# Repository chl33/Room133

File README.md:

# Room133 (v1.0.0)

Room133 is an ESP32-based family of devices which helps with various room-monitoring tasks, particulary for use with [Home Assistant](https://www.home-assistant.io/).

## Features
- **Adaptive Web Interface:** A modern, responsive Svelte UI that automatically detects and displays only the hardware capabilities active on your specific board (Motion, Light, Leak, OLED).
- **Climate Monitoring:** SHTC3-based temperature and humidity tracking.
- **Motion & Presence:** Support for one or more PIR sensors.
- **Environmental Sensing:** Light level measurement and standing water (leak) detection.
- **Unified Configuration:** Standardized JSON API and a clean settings interface for tuning filters and thresholds.
- **Robust Networking:** Automatic captive portal for WiFi setup and auto-reboot on configuration changes.
- **OTA Updates:** Reliable wireless firmware updates (requires `min_spiffs.csv` partition layout).

It is based on the [og3](https://github.com/chl33/og3) C++ software framework.

This repository includes software for the device, KiCAD files for the circuit board, and OpenSCAD files for creating the project boxes for the different devices.

Please see the [write-up](https://selectiveappeal.org/posts/room133/) on the project in my blog.  I also [wrote about](https://selectiveappeal.org/posts/room133-box/) the EBox design included in this repository.

## PCBA design: KiCAD

This project contains KiCAD sources for the Room133 circuit board.  It requires the [chl33_kicad_sym](https://github.com/chl33/chl33_kicad_sym) library.  I'm not experienced with sharing KiCAD projects in github.  I expect you will need to fix some path names if you try to open this project in KiCAD.

## EBox design: OpenSCAD

This project contains OpenSCAD sources for 3D-printing EBoxes for Room133 devices.  They use the library in [ProjectBox](https://github.com/chl33/ProjectBox).

You can open [`Ebox/Room133_test.scad`](Ebox/Room133_test.scad) with OpenSCAD and run [`Ebox/gui.sh`](Ebox/gui.sh), and use the user interface to customize the box depending on the application

.

I slice my EBox models with PrusaSlicer and print them in PETG.

## Wires

### PIR wire

JST socket 3x1

| Pin 1 | Pin2 | Pin 3  |
|:------|:-----|:-------|
| +5V   | GND  | Motion |

to

Dupont socket 3x1

| Pin 1 | Pin2 |  Pin 3  |
|:------|:------|:-------|
| +5V   | Motion| GND    |

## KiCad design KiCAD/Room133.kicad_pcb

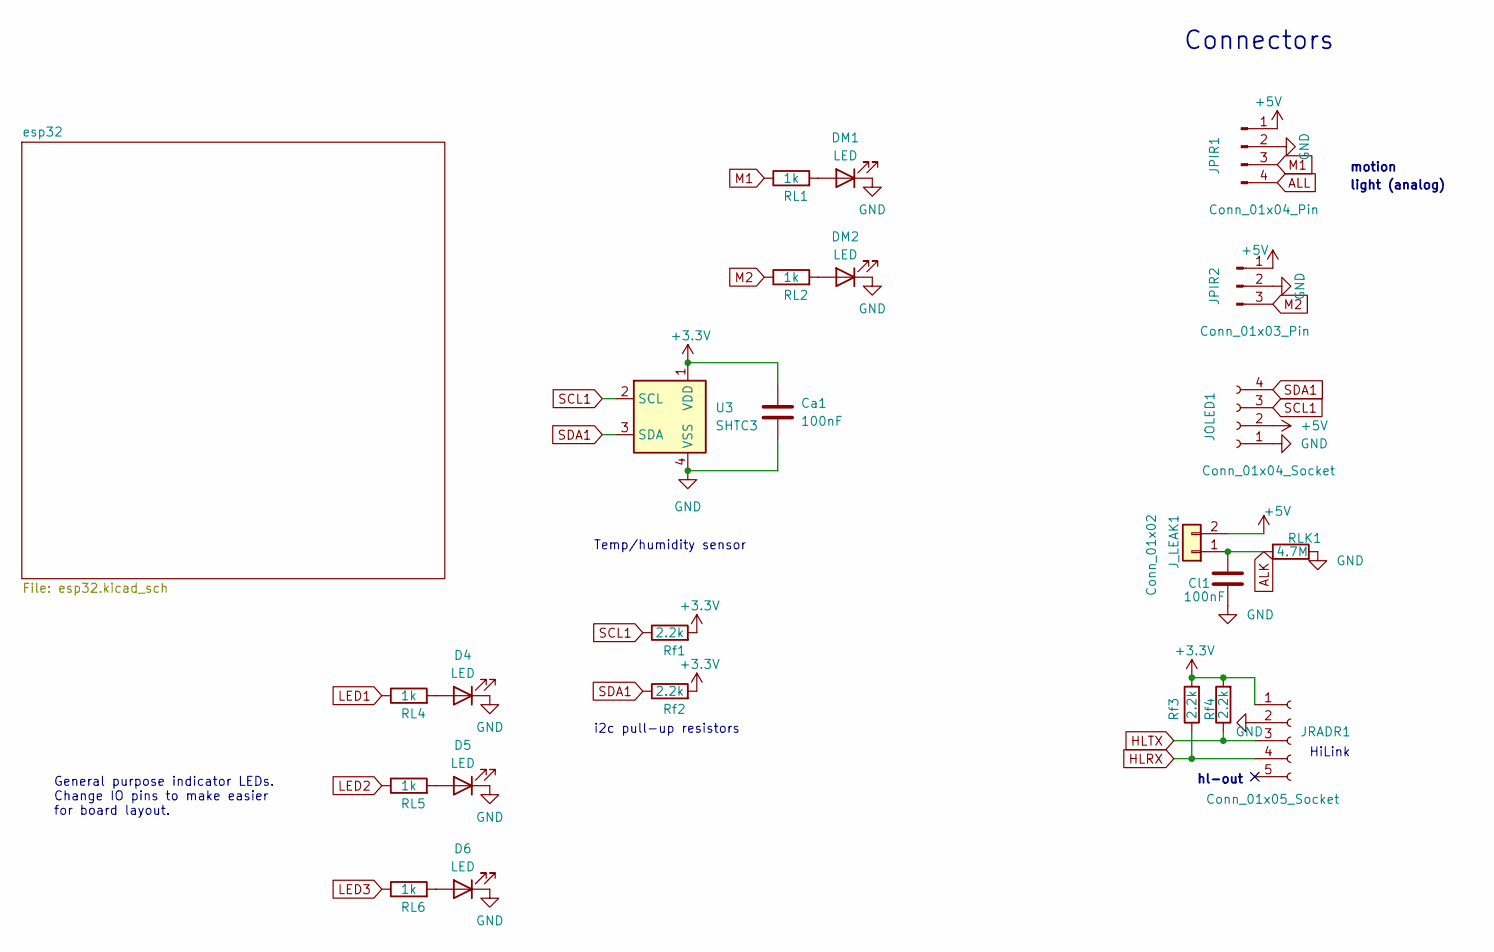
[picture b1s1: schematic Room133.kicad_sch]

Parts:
Ca1: 100nF; C_0603_1608Metric
Cl1: 100nF; C_0603_1608Metric
D4, D5, D6: LED; LED_0603_1608Metric
DM1, DM2: LED; LED_0603_1608Metric
JOLED1: Conn_01x04_Socket; PinSocket_1x04_P2.54mm_Vertical
JPIR1: Conn_01x04_Pin; JST_XH_B4B-XH-A_1x04_P2.50mm_Vertical
JPIR2: Conn_01x03_Pin; JST_XH_B3B-XH-A_1x03_P2.50mm_Vertical
JRADR1: Conn_01x05_Socket; PinSocket_1x05_P2.54mm_Vertical
J_LEAK1: Conn_01x02; JST_XH_B2B-XH-A_1x02_P2.50mm_Vertical
RL1, RL2, RL4, RL5, RL6: 1k; R_0603_1608Metric
RLK1: 4.7M; R_0603_1608Metric
Rf1, Rf2, Rf3, Rf4: 2.2k; R_0603_1608Metric
U3: SHTC3; Sensirion_DFN-4-1EP_2x2mm_P1mm_EP0.7x1.6mm

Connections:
+3.3V: Ca1.1, JRADR1.1, Rf1.2, Rf2.2, Rf3.2, Rf4.2, U3.1 (VDD); also elsewhere on the board
+5V: JOLED1.2, JPIR1.1, JPIR2.1, J_LEAK1.2; also elsewhere on the board
ALK: Cl1.1, J_LEAK1.1, RLK1.1; also elsewhere on the board
ALL: JPIR1.4; also elsewhere on the board
GND: Ca1.2, Cl1.2, D4.1 (K), D5.1 (K), D6.1 (K), DM1.1 (K), DM2.1 (K), JOLED1.1, JPIR1.2, JPIR2.2, JRADR1.2, RLK1.2, U3.4 (VSS); also elsewhere on the board
HLRX: JRADR1.4, Rf3.1; also elsewhere on the board
HLTX: JRADR1.3, Rf4.1; also elsewhere on the board
LED1: RL4.1; also elsewhere on the board
LED2: RL5.1; also elsewhere on the board
LED3: RL6.1; also elsewhere on the board
M1: JPIR1.3, RL1.1; also elsewhere on the board
M2: JPIR2.3, RL2.1; also elsewhere on the board
unnamed: D4.2 (A), RL4.2
unnamed: D5.2 (A), RL5.2
unnamed: D6.2 (A), RL6.2
unnamed: DM1.2 (A), RL1.2
unnamed: DM2.2 (A), RL2.2
SCL1: JOLED1.3, Rf1.1, U3.2 (SCL); also elsewhere on the board
SDA1: JOLED1.4, Rf2.1, U3.3 (SDA); also elsewhere on the board

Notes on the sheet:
Connectors
HiLink
hl-out
General purpose indicator LEDs. Change IO pins to make easier for board layout.
light (analog)
Temp/humidity sensor
motion
i2c pull-up resistors

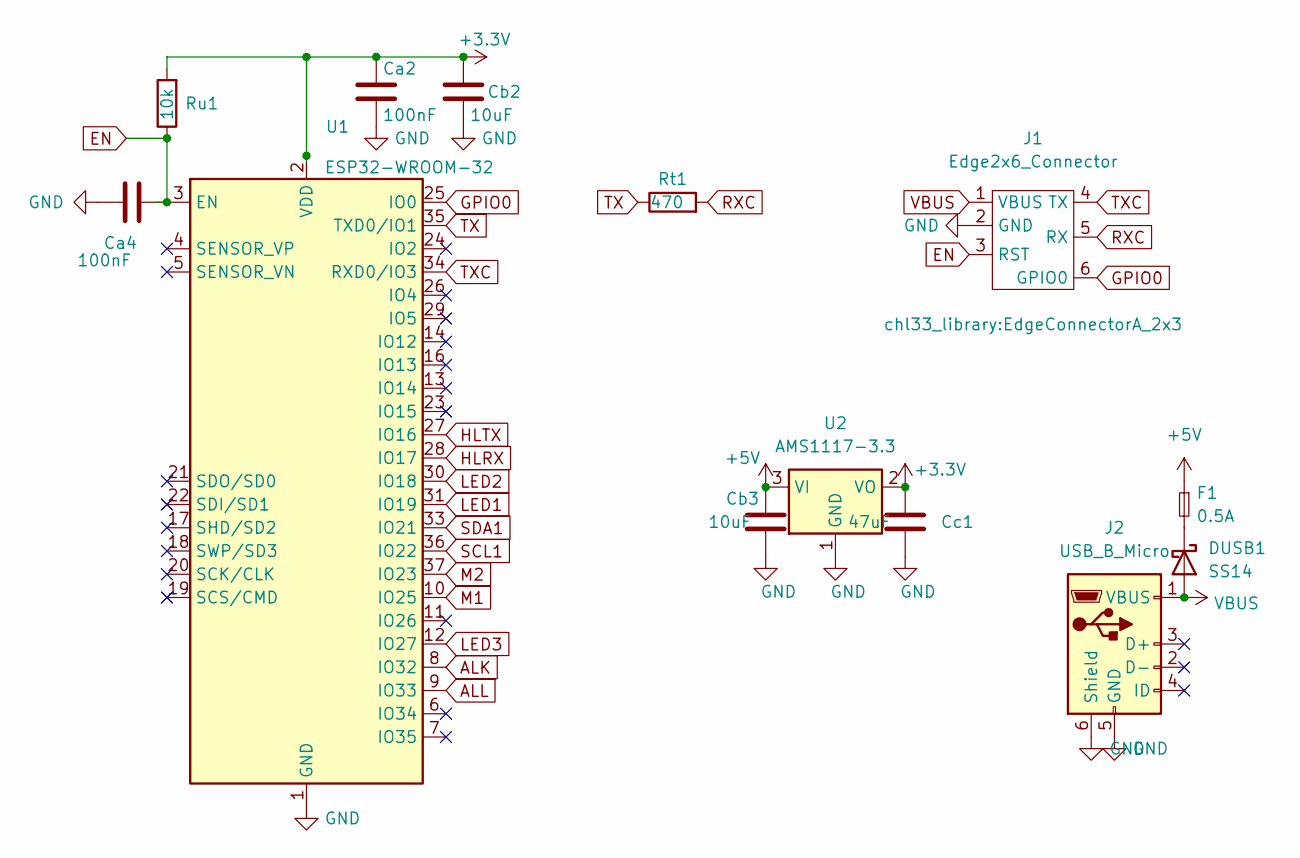
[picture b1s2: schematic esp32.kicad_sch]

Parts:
Ca2, Ca4: 100nF; C_0603_1608Metric
Cb2, Cb3: 10uF; C_0805_2012Metric_Pad1.18x1.45mm_HandSolder
Cc1: 47uF; C_0805_2012Metric_Pad1.18x1.45mm_HandSolder
DUSB1: SS14; D_2010_5025Metric
F1: 0.5A; D_0805_2012Metric
J1: Edge2x6_Connector; EdgeConnectorA_2x3
J2: USB_B_Micro; USB_Micro-B_Amphenol_10118194_Horizontal
Rt1: 470; R_0603_1608Metric
Ru1: 10k; R_0603_1608Metric
U1: ESP32-WROOM-32
U2: AMS1117-3.3; SOT-223-3_TabPin2

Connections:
+3.3V: Ca2.1, Cb2.1, Cc1.1, Ru1.2, U1.2 (VDD), U2.2 (VO); also elsewhere on the board
+5V: Cb3.1, F1.1, U2.3 (VI); also elsewhere on the board
ALK: U1.8 (IO32); also elsewhere on the board
ALL: U1.9 (IO33); also elsewhere on the board
EN: Ca4.2, J1.3 (RST), Ru1.1, U1.3 (EN)
GND: Ca2.2, Ca4.1, Cb2.2, Cb3.2, Cc1.2, J1.2 (GND), J2.5 (GND), J2.6 (Shield), U1.1 (GND), U1.15 (GND), U1.38 (GND), U1.39 (GND), U2.1 (GND); also elsewhere on the board
GPIO0: J1.6 (GPIO0), U1.25 (IO0)
HLRX: U1.28 (IO17); also elsewhere on the board
HLTX: U1.27 (IO16); also elsewhere on the board
LED1: U1.31 (IO19); also elsewhere on the board
LED2: U1.30 (IO18); also elsewhere on the board
LED3: U1.12 (IO27); also elsewhere on the board
M1: U1.10 (IO25); also elsewhere on the board
M2: U1.37 (IO23); also elsewhere on the board
unnamed: DUSB1.1 (K), F1.2
RXC: J1.5 (RX), Rt1.2
SCL1: U1.36 (IO22); also elsewhere on the board
SDA1: U1.33 (IO21); also elsewhere on the board
TX: Rt1.1, U1.35 (TXD0/IO1)
TXC: J1.4 (TX), U1.34 (RXD0/IO3)
VBUS: DUSB1.2 (A), J1.1 (VBUS), J2.1 (VBUS)

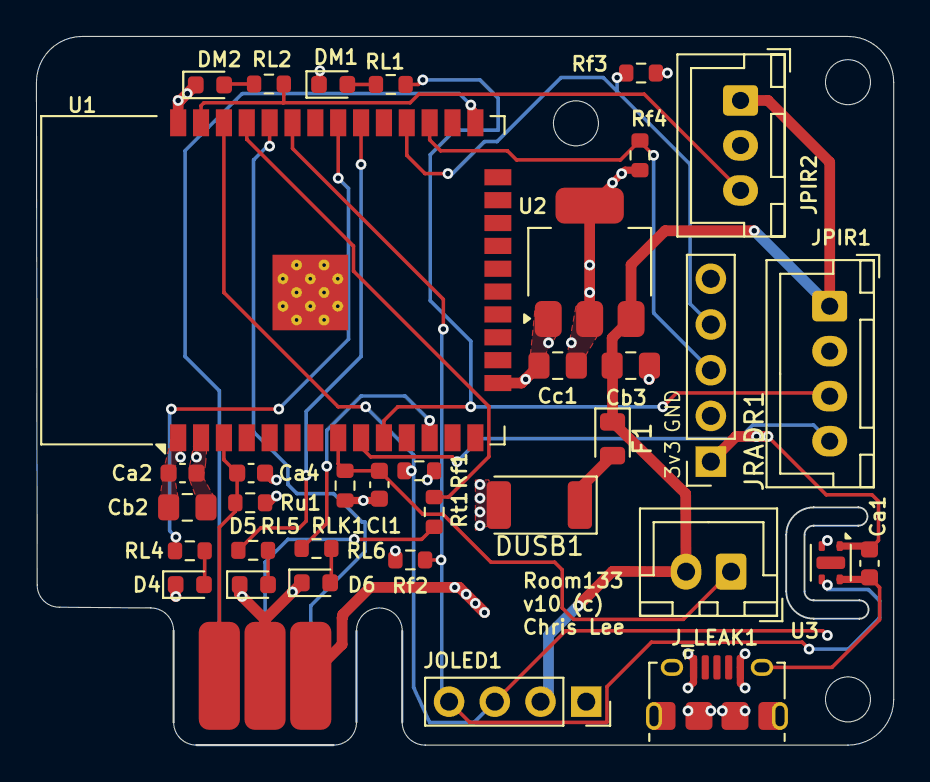
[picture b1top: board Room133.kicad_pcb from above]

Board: 4 copper layers, 47.6 x 39.3 mm, 36 parts (0 on the bottom side), 26 nets.

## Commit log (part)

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2024-08-24 Initial import of Room133 PlatformIO project
2024-08-24 added pre-commit formatting hook
2024-08-24 Minor fixes
    - dependency updates
    - add sample configuration file
2024-08-24 add copyright check
2024-08-24 platformio build action
2024-08-24 Minor fixes (#1)
    - dependency updates
    - add sample configuration file
    - add copyright check
    - add platformio build action
2024-08-24 add KiCAD sources for PCB
2024-08-24 add KiCAD sources for PCB (#2)
2024-08-24 fix github workflow path
2024-08-24 add example secrets file to support build check on GitHub
2024-08-24 add utility files
2024-08-24 platformio.ini update
2024-08-24 KiCAD files and workflow fix (#3)
    * add KiCAD sources for PCB
    * fix github workflow path
    * add example secrets file to support build check on GitHub
    * add utility files
    * platformio.ini update
2024-08-24 OpenSCAD Ebox
2024-08-24 copyrights
2024-08-24 clang-format
2024-08-24 OpenSCAD Ebox (#4)
    * OpenSCAD Ebox
    * copyrights
    * clang-format
2024-08-24 mention ebox in README
2024-08-24 mention ebox in README (#5)
2024-09-16 EBox updates made when writing blog entry
2024-09-16 Updates related to blog writeups (#6)
    * EBox updates made when writing blog entry
    * updated README
2024-09-16 typo
2024-09-17 add a base for supporting the radar box
2024-09-22 make top of radar bubble extra thin (on layer at 0.4mm)
2024-09-25 radar box (#7)
    * add a base for supporting the radar box
    * make top of radar bubble extra thin (on layer at 0.4mm)
2024-10-19 update dependencies
2024-10-19 update platformio ci test
2024-10-19 update deps (#8)
    * update dependencies
    * update platformio ci test
2024-10-24 update workflows
2024-10-24 update deps
2024-10-24 update workflows (#9)
    * update workflows
    * update deps
2025-01-01 update og3 to 0.2.5 (#10)
2025-01-02 Use interrupts, fix hardware support, og3 0.2.6
2025-01-02 Use interrupts, fix hardware support, og3 0.2.6 (#11)
2025-01-02 fix pin assignments on old vs new boards
2025-01-02 fix pin assignments on old vs new boards (#12)
2025-01-02 Update KiCad design
    Two LEDs were driven using input-only pins (gpio34,gpio35),
    so moved to gpio18, gpio19.
    Fixed library for edge footprint
2025-01-02 New board design allows use of 2 more LEDs
2025-01-18 Update ebox for board v10
2025-01-18 add boardV10 to secrets.ini.example
2025-01-18 add PIR wire spec
2025-01-18 Updates for v10 Room133 board (#13)
    - Update KiCad design
    - SHTC3 has better thermal isolation. Ebox updated for its new position.
    - Fixed library for edge footprint
    - Two LEDs were driven using input-only pins (gpio34,gpio35), so moved to gpio18, gpio19.
    - Updated to KiCAD 8.0 format
    - Documentation for PIR wire.
2025-01-19 No longer supporting older boards
2025-01-19 No longer supporting older boards (#14)
2025-08-24 upgrade og3 to version 0.3.90
2025-09-30 og3 -> 0.3.91
2025-10-11 use og3 version 0.3.92
2025-10-11 more std::string -> String to reduce differences with main branch
2025-10-11 version 0.9.91: dependency updates (#15)
2026-02-21 license header updates
2026-02-21 dependency version updates
2026-02-21 Version 0.9.92: newer og3 (#16)
    * license header updates
    * dependency version updates: og3 0.4.4
2026-02-21 platformio.ini and log tweaks
2026-02-22 license header update
2026-02-22 tweaks (#17)
    * platformio.ini and log tweaks
    * license header update
2026-03-01 use og3, which uses different web server and mqtt client
2026-03-02 Gemini changes for latest og3 changes
2026-03-09 updates from gemini to better organize build environment
2026-03-09 platformio.ini: use published versions of libraries
2026-03-09 update example build files
2026-03-09 use og3 version 0.5.0 (#18)
    * use og3 0.5.0, which uses different web server and mqtt client
    * updates from gemini to better organize build environment
    * update example build files
2026-03-25 Updates for og3 0.6.0 (gemini)
2026-03-27 Depend on published versions of libraries.
2026-04-04 add dependabot
2026-04-04 Added Svelte interface (gemini)
2026-04-04 fixes for svelte interface, wifi config, software version
2026-04-04 update github build action
2026-04-04 fix motion-detection display
2026-04-04 Set pulldown mode on PIR pins, show board name in web interface
2026-04-04 deps: use published og3 versions
2026-04-04 preparation for v1.0.0 release
2026-04-04 README -- show web UI
2026-04-04 Version 1.0.0 (#19)
    ### Added
    - **Dynamic Svelte Web Interface**: A completely new, responsive web interface that adapts to the board's hardware configuration.
    - **JSON API**: Full API support for status, configuration, WiFi, and MQTT settings using the `camelCase` standard.
    ### Changed
    - **Standardized Naming**: All API keys and internal variables migrated to `camelCase` for consistency across the Room133/Plant133/Garden133 family.
    - **Legacy Interface Migration**: The old HTML-only interface has been moved to `/old` and `/old_config`.
2026-04-04 Bump actions/checkout from 4 to 6
    Bumps [actions/checkout](https://github.com/actions/checkout) from 4 to 6.
    - [Release notes](https://github.com/actions/checkout/releases)
    - [Changelog](https://github.com/actions/checkout/blob/main/CHANGELOG.md)
    - [Commits](https://github.com/actions/checkout/compare/v4...v6)
    ---
    updated-dependencies:
2026-04-04 Bump actions/setup-node from 4 to 6
    Bumps [actions/setup-node](https://github.com/actions/setup-node) from 4 to 6.
    - [Release notes](https://github.com/actions/setup-node/releases)
    - [Commits](https://github.com/actions/setup-node/compare/v4...v6)
    ---
    updated-dependencies:
    - dependency-name: actions/setup-node
2026-04-04 Bump actions/setup-python from 5 to 6
    Bumps [actions/setup-python](https://github.com/actions/setup-python) from 5 to 6.
    - [Release notes](https://github.com/actions/setup-python/releases)
    - [Commits](https://github.com/actions/setup-python/compare/v5...v6)
    ---
    updated-dependencies:
    - dependency-name: actions/setup-python
2026-04-04 Bump actions/setup-python from 5 to 6 (#22)
    Bumps [actions/setup-python](https://github.com/actions/setup-python) from 5 to 6.
    - [Release notes](https://github.com/actions/setup-python/releases)
    - [Commits](https://github.com/actions/setup-python/compare/v5...v6)
    ---
    updated-dependencies:
    - dependency-name: actions/setup-python
2026-04-04 Bump actions/setup-node from 4 to 6 (#21)
    Bumps [actions/setup-node](https://github.com/actions/setup-node) from 4 to 6.
    - [Release notes](https://github.com/actions/setup-node/releases)
    - [Commits](https://github.com/actions/setup-node/compare/v4...v6)
    ---
    updated-dependencies:
    - dependency-name: actions/setup-node
2026-04-04 Bump actions/checkout from 4 to 6 (#20)
    Bumps [actions/checkout](https://github.com/actions/checkout) from 4 to 6.
    - [Release notes](https://github.com/actions/checkout/releases)
    - [Changelog](https://github.com/actions/checkout/blob/main/CHANGELOG.md)
    - [Commits](https://github.com/actions/checkout/compare/v4...v6)
    ---
    updated-dependencies:
2026-06-19 Bump actions/checkout from 6 to 7
    Bumps [actions/checkout](https://github.com/actions/checkout) from 6 to 7.
    - [Release notes](https://github.com/actions/checkout/releases)
    - [Changelog](https://github.com/actions/checkout/blob/main/CHANGELOG.md)
    - [Commits](https://github.com/actions/checkout/compare/v6...v7)
    ---
    updated-dependencies:
2026-06-19 Bump actions/checkout from 6 to 7 (#23)
    Bumps [actions/checkout](https://github.com/actions/checkout) from 6 to 7.
    - [Release notes](https://github.com/actions/checkout/releases)
    - [Changelog](https://github.com/actions/checkout/blob/main/CHANGELOG.md)
    - [Commits](https://github.com/actions/checkout/compare/v6...v7)
    ---
    updated-dependencies:
2026-06-24 Bump actions/cache from 5 to 6
    Bumps [actions/cache](https://github.com/actions/cache) from 5 to 6.
    - [Release notes](https://github.com/actions/cache/releases)
    - [Changelog](https://github.com/actions/cache/blob/main/RELEASES.md)
    - [Commits](https://github.com/actions/cache/compare/v5...v6)
    ---
    updated-dependencies:
